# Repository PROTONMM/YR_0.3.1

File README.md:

# PCB and Enclosure for the Yoradio Internet Radio

This project includes **only** the PCB and the enclosure; it does **not** include any software. MIT License.

<span style="color:red">**WARNING: This project is intended for advanced users. It is meant for further expansion and modification.**</span>

## Versions

Two enclosure versions are provided: one as a kitchen radio with speakers, and another with an RCA output for connecting to an external amplifier.

### RCA Version

### With speakers version 

## Key components

The design was created around a few specific key parts; using other variants may require adjusting the enclosure and the PCB accordingly.

### Display

Only for SSD1322 display

### Encoder

https://pl.aliexpress.com/item/1005003534390893.html

### Knob

For the encoder above, you need the `Flower Shaped` variant.

https://pl.aliexpress.com/item/1005006912587864.html

### Speakers

https://pl.aliexpress.com/item/1005008571777367.html

### Less important parts

Personally, as the DAC and amplifier I used the **WeAct Studio I2S Speaker Module PCM5100A 4Ω 2.8W D Class Dual PA**.

https://pl.aliexpress.com/item/1005009660188314.html

### Acknowledgements

Special thanks to **Inżynier Programista** for help solving FreeCAD issues. Link to his YouTube channel: https://www.youtube.com/@InzynierProgramista

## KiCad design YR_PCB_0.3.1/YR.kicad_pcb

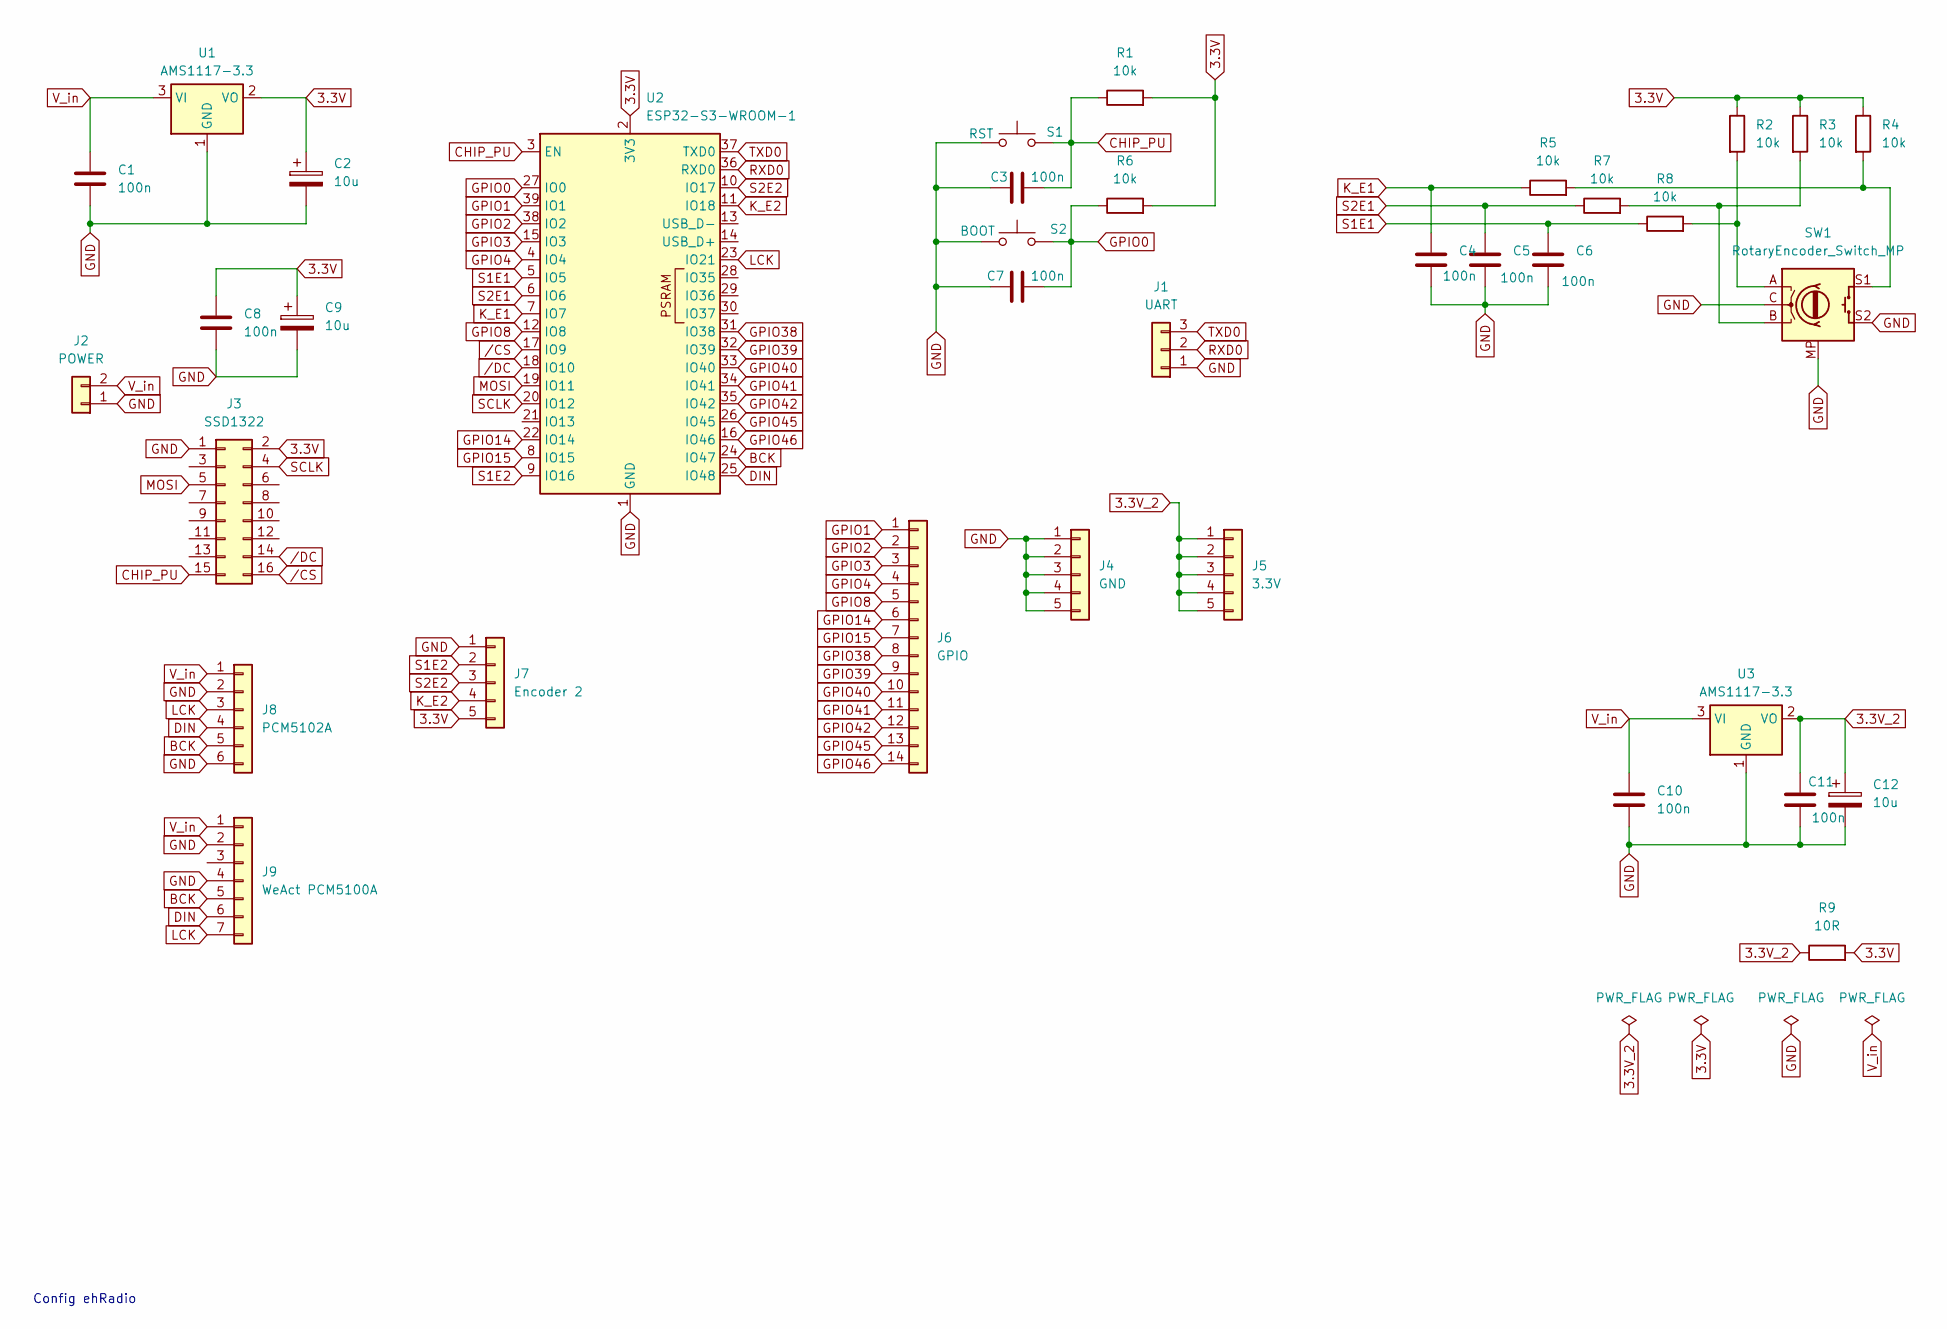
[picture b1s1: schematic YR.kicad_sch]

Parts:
C1, C3, C4, C5, C6, C7, C8, C10, C11: 100n; C_1206_3216Metric_Pad1.33x1.80mm_HandSolder
C2, C9, C12: 10u; CP_Elec_4x3.9
J1: UART; PinHeader_1x03_P2.54mm_Vertical
J2: POWER; JST_XH_B2B-XH-A_1x02_P2.50mm_Vertical
J3: SSD1322; PinSocket_2x08_P2.54mm_Vertical
J4: GND; PinHeader_1x05_P2.54mm_Vertical
J5: 3.3V; PinHeader_1x05_P2.54mm_Vertical
J6: GPIO; PinHeader_1x14_P2.54mm_Vertical
J7: Encoder 2; PinHeader_1x05_P2.54mm_Vertical
J8: PCM5102A; PinHeader_1x06_P2.54mm_Vertical
J9: WeAct PCM5100A; PinHeader_1x07_P2.54mm_Vertical
R1, R2, R3, R4, R5, R6, R7, R8: 10k; R_1206_3216Metric_Pad1.30x1.75mm_HandSolder
R9: 10R; R_1206_3216Metric_Pad1.30x1.75mm_HandSolder
S1: RST; SW_SPST_TS-1088-xR025
S2: BOOT; SW_SPST_TS-1088-xR025
SW1: RotaryEncoder_Switch_MP; RotaryEncoder_Alps_EC11E-Switch_Vertical_H20mm_CircularMoun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
U1, U3: AMS1117-3.3; SOT-223-3_TabPin2
U2: ESP32-S3-WROOM-1

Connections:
3.3V: C2.1, C8.1, C9.1, J3.2, J7.5, R1.2, R2.1, R3.1, R4.1, R6.2, R9.2, U1.2 (VO), U2.2 (3V3)
3.3V_2: C11.1, C12.1, J5.1, J5.2, J5.3, J5.4, J5.5, R9.1, U3.2 (VO)
BCK: J8.5, J9.5, U2.24 (IO47)
CHIP_PU: C3.2, J3.15, R1.1, S1.2, U2.3 (EN)
DIN: J8.4, J9.6, U2.25 (IO48)
GND: C1.2, C2.2, C3.1, C4.2, C5.2, C6.2, C7.1, C8.2, C9.2, C10.2, C11.2, C12.2, J1.1, J2.1, J3.1, J4.1, J4.2, J4.3, J4.4, J4.5, J7.1, J8.2, J8.6, J9.2, J9.4, S1.1, S2.1, SW1.C, SW1.MP, SW1.S2, U1.1 (GND), U2.1 (GND), U2.40 (GND), U2.41 (GND), U3.1 (GND)
GPIO0: C7.2, R6.1, S2.2, U2.27 (IO0)
GPIO1: J6.1, U2.39 (IO1)
GPIO2: J6.2, U2.38 (IO2)
GPIO3: J6.3, U2.15 (IO3)
GPIO4: J6.4, U2.4 (IO4)
GPIO8: J6.5, U2.12 (IO8)
GPIO14: J6.6, U2.22 (IO14)
GPIO15: J6.7, U2.8 (IO15)
GPIO38: J6.8, U2.31 (IO38)
GPIO39: J6.9, U2.32 (IO39)
GPIO40: J6.10, U2.33 (IO40)
GPIO41: J6.11, U2.34 (IO41)
GPIO42: J6.12, U2.35 (IO42)
GPIO45: J6.13, U2.26 (IO45)
GPIO46: J6.14, U2.16 (IO46)
K_E1: C4.1, R5.1, U2.7 (IO7)
K_E2: J7.4, U2.11 (IO18)
LCK: J8.3, J9.7, U2.23 (IO21)
MOSI: J3.5, U2.19 (IO11)
unnamed: R2.2, R8.2, SW1.A
unnamed: R3.2, R7.2, SW1.B
unnamed: R4.2, R5.2, SW1.S1
RXD0: J1.2, U2.36 (RXD0)
S1E1: C6.1, R8.1, U2.5 (IO5)
S1E2: J7.2, U2.9 (IO16)
S2E1: C5.1, R7.1, U2.6 (IO6)
S2E2: J7.3, U2.10 (IO17)
SCLK: J3.4, U2.20 (IO12)
TXD0: J1.3, U2.37 (TXD0)
V_in: C1.1, C10.1, J2.2, J8.1, J9.1, U1.3 (VI), U3.3 (VI)
/CS: J3.16, U2.17 (IO9)
/DC: J3.14, U2.18 (IO10)

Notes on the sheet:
Config ehRadio

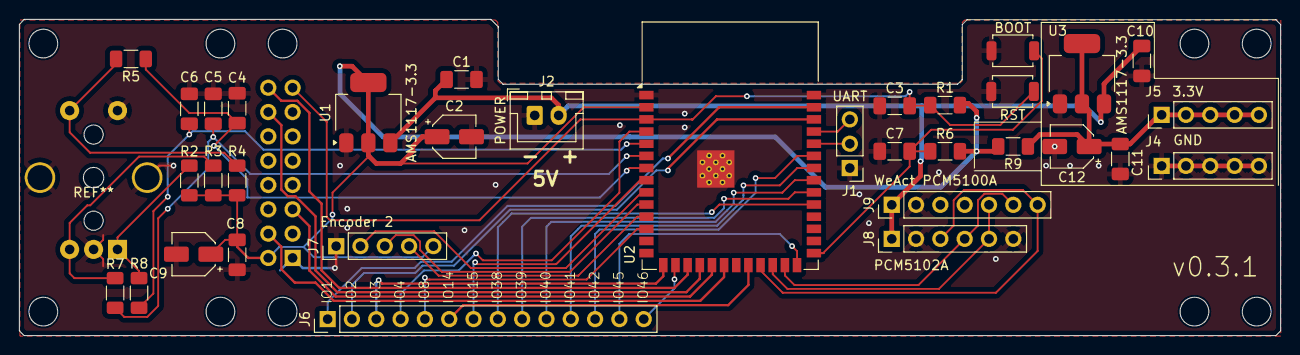
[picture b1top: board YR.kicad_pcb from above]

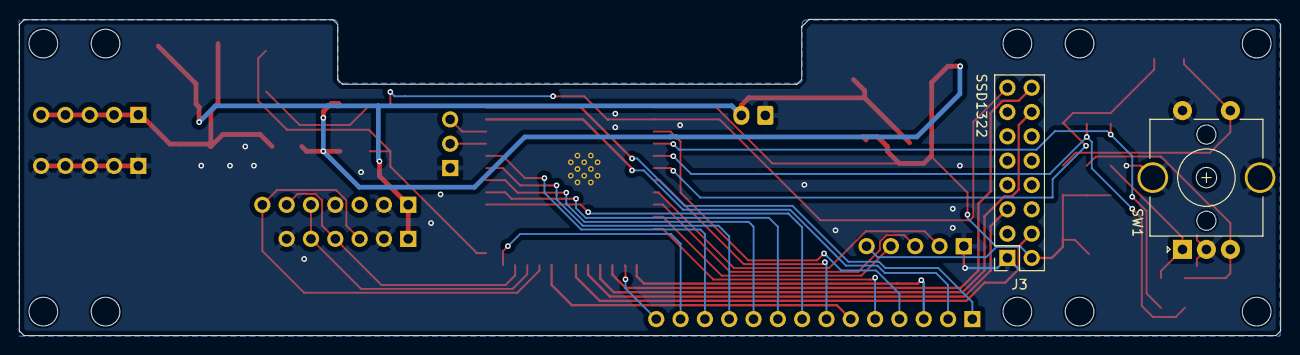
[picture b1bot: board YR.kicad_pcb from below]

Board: 2 copper layers, 131.8 x 33.0 mm, 36 parts (2 on the bottom side), 38 nets.

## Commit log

2026-01-31 added PCB
2026-01-31 added FreeCAD cases projects
2026-01-31 added README.md
2026-01-31 fix README.md
2026-02-02 added SSD1322 to README.md
2026-02-02 added myoptions.h
